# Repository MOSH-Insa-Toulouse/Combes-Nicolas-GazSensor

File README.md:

# Création d’un shield LoRa pour Arduino

Année scolaire 2018/2019

## Travaux pratiques de Micro-controleurs et open-source hardware

### Introduction : 

Au cours de travaux pratique, nous allons nous familiariser avec le logiciel KiCad. Pour cela, nous allons réaliser le schéma électronique d’un shield Arduino, associer une empreintes à chaque composant en en modifiant certaines puis réaliser le schéma de routage  du circuit imprimé. Ce shield aura pour but d’être connecté sur une carte arduino uno afin qu’elle puisse communiquer en LoRa, le schéma électronique sera alors composé d’une partie instrumentation contenant un capteur de gaz ainsi que de connecteurs pour brancher une carte LoRa. Nous utiliserons ensuite se travail pour utiliser un capteur de gaz que nous allons réaliser en stage à l’AIME

### I Création d’un symbole LTC1050

Dans un premier temps nous avons utilisé l’éditeur de librairies de symboles pour créer un symbole personnalisé pour l’AOP LTC1050. Ce composant n’est pas dans la bibliothèque Linear est fait partie du circuit d’instrumentation.

Ici, on a dans un premier temps fait un schéma pour choisir la forme du symbole, ensuite nous avons ajouté des pin en précisant leur type (passif, alimentation…), leur numéro et leur nom. Il y a deux pins non connecté car ce composant est construit avec 8 pattes dont 2 qui n’ont pas d’utilité.

### II Réalisation du schéma électronique

Ensuite, maintenant que nous avions tous les symboles nécessaires pour notre circuit électronique, nous avons réalisé celui-ci.

Nous avons choisi quels composant ajouter au schéma en leur donnent un nom et une valeur. Pour connecter les différentes parties du schéma, nous avons utilisé des labels.
Pour la partie instrumentation nous nous somme basés sur le schéma suivant.

Ici, on a simulé le capteur de gaz par une résistance variable, en effet le capteur que nous allons réaliser est un capteur résistif. Cet étage d’instrumentation sert à adapter la mesure du capteur pour qu’elle puisse être interprétée par la carte Arduino. La variation de résistance induit une variation de tension sur la sortie qui sera connecté à une entrée analogique de la carte Arduino.

### III Association d’empreintes

Une fois notre schéma électronique terminé, nous avons associé des empreintes à chaque composant. Pour trouver quelle empreinte associer à quel composant, nous avons regarder la taille des composant disponibles à l’INSA et choisi des empreintes adaptées. Pour le LTC1050, nous avons regardé dans la documentation technique, partie « Package Information » car nous n’avons pas se composant à l’INSA.

### IV Réalisation du schéma de routage

Ensuite nous avons réalisé le schéma de routage pour les circuits imprimé.

Ici on voit qu’une connexion n’est pas faite, cela permettra de réaliser le circuit en simple-face, elle sera réalisée avec un fil.

### Auteurs : 

Nicolas Damien

Combes Jules

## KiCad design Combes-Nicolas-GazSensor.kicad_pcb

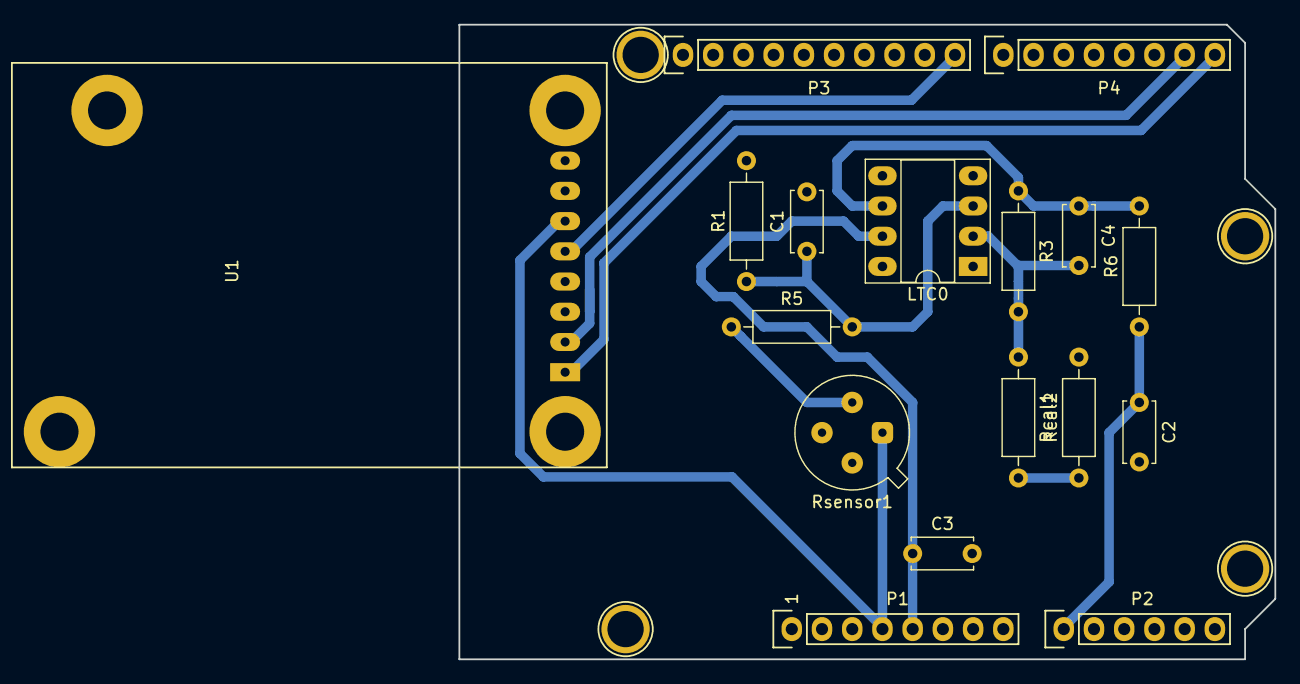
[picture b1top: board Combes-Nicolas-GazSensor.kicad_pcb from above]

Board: 2 copper layers, 68.6 x 53.3 mm, 21 parts (0 on the bottom side), 12 nets.

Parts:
C1, C2, C3: 100n; C_Disc_D5.0mm_W2.5mm_P5.00mm
C4: 1u; C_Disc_D5.0mm_W2.5mm_P5.00mm
LTC0: LTC1050; DIP-8_W7.62mm_Socket_LongPads
P1: Power; Socket_Strip_Arduino_1x08
P2: Analog; Socket_Strip_Arduino_1x06
P3: Digital; Socket_Strip_Arduino_1x10
P4: Digital; Socket_Strip_Arduino_1x08
P5, P6, P7, P8: CONN_01X01; Arduino_1pin
R1, R3: 100k; R_Axial_DIN0207_L6.3mm_D2.5mm_P10.16mm_Horizontal
R5: 10k; R_Axial_DIN0207_L6.3mm_D2.5mm_P10.16mm_Horizontal
R6: 1k; R_Axial_DIN0207_L6.3mm_D2.5mm_P10.16mm_Horizontal
Rcal1: 1k; R_Axial_DIN0207_L6.3mm_D2.5mm_P10.16mm_Horizontal
Rcal2: 220; R_Axial_DIN0207_L6.3mm_D2.5mm_P10.16mm_Horizontal
Rsensor1: 10k<...<1G; TO-5-4
U1: RN2483_Breakout

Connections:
+3V3: P1.4, Rsensor1.1, U1.6
+5V: C3.1, LTC0.7, P1.5
A0: C2.1, P2.1, R6.1
D8: P3.10, U1.5
GND: C1.2, C2.2, C3.2, LTC0.4, P1.6, P1.7, P3.4, R1.2, Rcal2.2, U1.8
unnamed: C1.1, LTC0.3, R1.1, R5.2
unnamed: C4.1, LTC0.6, R3.1, R6.2
unnamed: C4.2, LTC0.2, R3.2, Rcal1.1
unnamed: R5.1, Rsensor1.2
unnamed: Rcal1.2, Rcal2.1
Rx: P4.8, U1.1
Tx: P4.7, U1.2

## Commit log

2018-10-31 Demarrage de notre projet
2018-10-31 Shield Capteur
2018-11-14 Version avec RN2483 Breakout et routage
2018-11-29 Mise à jour du readme
